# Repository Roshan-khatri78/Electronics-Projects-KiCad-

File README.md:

# ⚡ KiCad Projects Portfolio
 
A collection of electronics projects I designed in **KiCad**: schematics, PCB layouts, 3D models and, for many of them, Gerber files. I use it to learn by building, and every project here taught me something, including the mistakes. New projects get added as I go.

---
 
## 🌟 Featured: 4G GPS Tracker (4-layer)
 
[**Open the project folder →**](./4G-GPS-Tracker/)
 
My biggest and most complex design so far: a 4-layer 4G GPS tracker board with an ESP32-S3 and a 4G modem with built-in GNSS. I redrew the whole schematic by hand as hierarchical sheets, assigned every footprint and 3D model, then placed and routed the full board.
 
> **This is a design-only project.** It is based on the public Waveshare ESP32-S3-SIM7670X-4G schematic, which I redrew in KiCad. It is not an original circuit design, and I have not ordered, built or tested the board.
 
<!-- Add your images in 4G-GPS-Tracker/docs/ and keep these names, or change the paths -->

### What is on the board
 
- ESP32-S3 and a SIM7670X 4G modem with GNSS
- Battery charging and protection (ETA6098 charger, DW01 + 8205 protection), solar charge input (CN3791), MAX17048 fuel gauge
- USB-C, 18650 battery holder, SIM slot, microSD card, camera connector, MEMS microphone
- 3 u.FL antenna connectors (4G, GNSS, Wi-Fi/BT)
- W25Q128 flash, TXB0104 level shifter, CH343P USB-UART, push buttons, a DIP switch and pin headers
### Numbers
 
| | |
|---|---|
| Layers | 4 |
| Nets | 285 |
| Pads | 1000 |
| Vias | 564 |
| Capacitors / resistors | 90+ / 84+ |
| Footprint size for passives | 0805 (2012 metric) |
| KiCad version | 10.0.3 |
 
### Stackup and routing choices
 
| Layer | Use |
|---|---|
| F.Cu | Components, signals and the RF lines |
| In1.Cu | Solid GND plane |
| In2.Cu | Signal routing (no power pour, power is routed with traces) |
| B.Cu | Signals and the battery connections |
 
- The antenna lines are routed as **50 Ω microstrip** on F.Cu above the solid In1 GND plane. The width is about 0.35 mm for a 0.2 mm dielectric. This is a **calculated** value, not a measured one.
- Every GND pad gets a via straight down to the In1 plane, so the board has no long GND traces.
- Via sizes: 0.6 / 0.3 mm in general, and 0.5 / 0.25 mm in tight areas such as the camera fan-out.
- The crystal has no traces under it, and the SPI flash sits close to the ESP32.
### Status
 
- All nets are routed (0 unrouted).
- The KiCad DRC window crashed on this board, so I run DRC from the command line with `kicad-cli`, using a small script (in [`tools/`](./tools/)). It groups the violations by type, so I can see the real problems first.
- <!-- UPDATE this line after your final DRC run --> First DRC run: 0 unconnected items and 511 violations. Most of them were a via-size rule setting and cosmetic items (silkscreen, solder mask slivers). I am cleaning them up. A few minor violations may remain, so please **run DRC yourself before judging the layout**.
### Known limits
 
I want to be upfront about these:
 
- Power traces are 0.25 to 0.35 mm wide to fit the dense layout. A production board would use 1 mm or wider traces (or pours) for the modem supply, and several vias per layer change.
- A few vias are placed inside pads. A real factory would need filled and capped vias, or the vias would move beside the pads.
- The GNSS connector is far from the modem's GNSS pad, so that trace is longer than it should be. A final layout would move the connector closer.
- The camera part (U15) does not match yet. The schematic uses a 24-pin socket, and the footprint is the bare camera package.
- Nothing is simulated or measured: not the RF lines, not the power rails.
### What I learned
 
The first netlist update gave 47 errors from wrong footprints and missing library names. ERC complained about power outputs until I fixed the pin types on the GND pins. My first GNSS antenna trace was 68 mm long and ran on the back layer under the modem, so I deleted it and routed it again on the top layer. Along the way I learned about microstrip width, via sizes, fan-out under a camera footprint and why vias do not belong in small pads. Next I want to learn LTspice, to simulate the power blocks and filters.
 
**Credit:** schematic reference is the Waveshare ESP32-S3-SIM7670X-4G board design.
 
---
 
## 📖 About
 
The projects here go from simple beginner circuits to a 4-layer board with a 4G modem. Each one reflects real learning, including mistakes, revisions and improvements over time.
 
**Skills practiced**
 
- Schematic capture and symbol assignment, hierarchical multi-sheet schematics
- Footprint selection and custom footprint and symbol library creation
- PCB layout, trace routing, copper pours, 4-layer stackups
- RF trace width for 50 Ω microstrip (calculated)
- DRC, ERC and design rules, including command-line DRC
- Gerber export for fabrication
- 3D model linking and visualisation
---
 
## 🗂️ All projects
 
### ⚙️ Power conversion and batteries
 
| Project | What it is |
|---|---|
| [3V to 40V DC Booster](./3v%20to%2040v%20DC%20booster/) | Boost converter that steps 3 V up to as much as 40 V |
| [60W SMPS](./60W%20SMPS/) | 60 W switch-mode power supply |
| [DC-DC Buck Converter](./DC-DC%20Buck%20converter/) | XL4015 step-down converter with constant-current / constant-voltage output |
| [Battery Desulfator](./Battery%20Desulfator%20circuit/) | NE555 pulse generator driving an IRF244V MOSFET, for lead-acid batteries |
| [Battery Powered Bench Power Supply](./Battery%20powered%20bench%20power%20supply/) | Bench power supply that runs from batteries |
| [Li-ion 4S BMS](./Li-ion%204S%20BMS/) | Battery management board for a 4-cell Li-ion pack |
| [TP4056 Module](./tp4056%20module/) | TP4056 Li-ion battery charger module |
| [Multi-rail PDB](./multirail%20PDB/) | 24 V to 12 V, 5 V and 3.3 V buck cascade with a TI eFuse on each rail |
| [YX850 Power Failure Switching Module](./YX850%20Power%20Failure%20Automatic%20Switching%20Module/) | Automatic switch-over module for power failures |
| [Mini Inverter](./mini%20inverter/) | DC to AC inverter using IR2153 half-bridge gate drive |
| [Induction Heater](./inductionheater/) | High-frequency switching circuit that heats metal with a work coil |
 
### 🔧 Motor drivers and switching
 
| Project | What it is |
|---|---|
| [1-Channel Relay Driver](./1channelrelay/) | MMBT2222A switching a relay, with a flyback diode and a GND pour |
| [3-Phase BLDC Motor Controller](./3-Phase%20BLDC%20%28Brushless%20DC%29%20Motor%20Controller/) | Hierarchical design with IR2104 gate drivers and a 3-phase MOSFET bridge |
| [A4988 Stepper Motor Driver](./A4988%20Stepper%20Motor%20Driver/) | Stepper motor driver board based on the A4988 |
| [L298 Motor Driver](./L298%20motor%20driver/) | Dual H-bridge driver for two DC motors or one stepper motor |
| [Dual VNH2SP30 Motor Driver](./Dual%20VNH2SP30%20Motor%20Driver%20Carrier%20MD03A/) | Carrier board for the dual VNH2SP30 high-current motor driver |
| [Solid-state Relay](./Solid-state%20relay/) | Solid-state relay circuit |
 
### 📡 Wireless, GNSS and radio
 
| Project | What it is |
|---|---|
| [4G GPS Tracker](./4G-GPS-Tracker/) | **Featured.** 4-layer board with ESP32-S3 and a 4G modem with GNSS |
| [Embedded GSM_GPS IoT Controller](./Embedded%20GSM_GPS%20IoT%20Controller/) | IoT controller board with GSM and GPS |
| [GSM_GPS Embedded Development Board](./GSM_GPS%20Embedded%20Development%20Board/) | Development board with GSM and GPS |
| [HC-06 Bluetooth Module](./HC-06%20BLUETOOTH%C2%AE%20Module/) | Breakout board for the HC-06 Bluetooth serial module |
| [Digital Radio Receiver](./microcontroller-controlled%20digital%20radio%20receiver/) | Microcontroller-tuned FM/AM radio receiver |
| [Portable FM Radio Receiver](./portable%20FM%20radio%20receiver/) | Battery-powered FM radio with an M6955 receiver IC and an Arduino Pro Mini |
| [FMCW Radar](./FMCW%20Radar/) | FMCW radar board |
| [Wake on LAN](./Wake%20on%20LAN/) | Wake-on-LAN board |
 
### 🧠 Microcontroller and computer boards
 
| Project | What it is |
|---|---|
| [Arduino Uno R3 Clone](./Arduino%20R3/) | Clone of the Arduino Uno R3 with the ATmega328P |
| [STM32 Dev Board](./STM32%20DEV%20board/) | STM32 board with reset, boot selection, crystal and programming header |
| [ESP32 Demo Project](./esp32%20demo%20project/) | ESP32 module board exploring power, GPIO and boot strapping pins |
| [ESP32-S3](./ESP32-S3/) | ESP32-S3 based board |
| [ESP32 Drone](./esp32Drone/) | ESP32 flight controller with IMU, ESC outputs and USB-C, 4 layers |
| [Mini Drone](./minidrone/) | Small drone board |
| [Raspberry Pi Pico](./rasberry%20pi%20pico/) | Raspberry Pi Pico board design |
| [Raspberry Pi CM4 Carrier Board](./Raspberry%20Pi%20Compute%20Module%204%20Carrier%20Board/) | Carrier board for the Raspberry Pi Compute Module 4 |
| [Milk-V Duo Module](./Milk-V%20Duo%20Module/) | Board design for the Milk-V Duo |
| [LoFive](./LoFive/) | RISC-V board based on the open-source LoFive design |
| [USB to UART Converter](./USB2UART/) | USB-serial bridge board for programming and debugging microcontrollers |
 
### 🔬 Sensors, analog, instruments and basics
 
| Project | What it is |
|---|---|
| [ESP32 Oscilloscope and Function Generator](./esp32%20oscilloscope%20adn%20fucntion%20generator/) 🎓 | **Final year project.** Signal acquisition and signal generation on one ESP32 board |
| [Air Quality Sensor Board](./Air%20Quality%20Sensor%20Board/) | Air quality sensor with an MCU and a Tag-Connect SWD footprint |
| [DS3231 RTC Module](./DS3231%20RTC%20Module/) | Real-time clock breakout with battery backup |
| [SPO2 Pulse Oximeter](./SPO2/) | Red and IR LEDs with a photodetector for SpO2 and heart rate |
| [VL53L0X ToF Distance Sensor](./VL53L0X%20Time-of-Flight%20Distance%20Sensor/) | Breakout for the VL53L0X time-of-flight sensor |
| [LM386 Audio Amplifier](./LM386%20Based%20Audio%20Amplifier/) | Small audio amplifier built around the LM386 |
| [Hearing Aid](./hearingaid/) | Hearing-aid amplifier with an electret mic, BC547 transistor stages and a 16 Ω earpiece on 3 V |
| [LED Flasher](./LED%20flasher/) | Astable multivibrator LED flasher |
| [One Digit Up/Down Counter](./one%20digit%20updown%20counter/) | Up/down counter with a 7-segment display |
| [Traffic Light Controller](./Traffic%20light%20controller/) | Traffic light controller circuit |
 
---
 
## 📁 Repository structure
 
Each project has its own folder. Most contain:
 
```
<project-name>/
├── *.kicad_sch      # Schematic files
├── *.kicad_pcb      # PCB layout files
└── Gerber/          # Fabrication files, where exported
```
 
The featured project also has a `docs/` folder with the 3D images and a `tools/` folder at the repository root with the command-line DRC script.
 
---
 
## 🛠️ Tools
 
- **KiCad EDA** v10.0
- `kicad-cli` for command-line DRC
- Manufacturer data sheets for part selection
- KiCad 3D viewer for visual inspection
- Custom symbol and footprint libraries
---
 
## 📝 Note on quality
 
These projects document my learning openly. Some designs have flaws or open points, and I list them where I know them. I come back and improve designs as my knowledge grows, instead of hiding earlier work.
 
---
 
## 📄 License
 
Unless stated otherwise, the projects here are shared for education and as a portfolio. Designs that are based on other people's work (for example the Waveshare reference design) belong to their original authors, and I credit them in each project.
 
Feel free to open an issue or a discussion if you have suggestions or feedback.

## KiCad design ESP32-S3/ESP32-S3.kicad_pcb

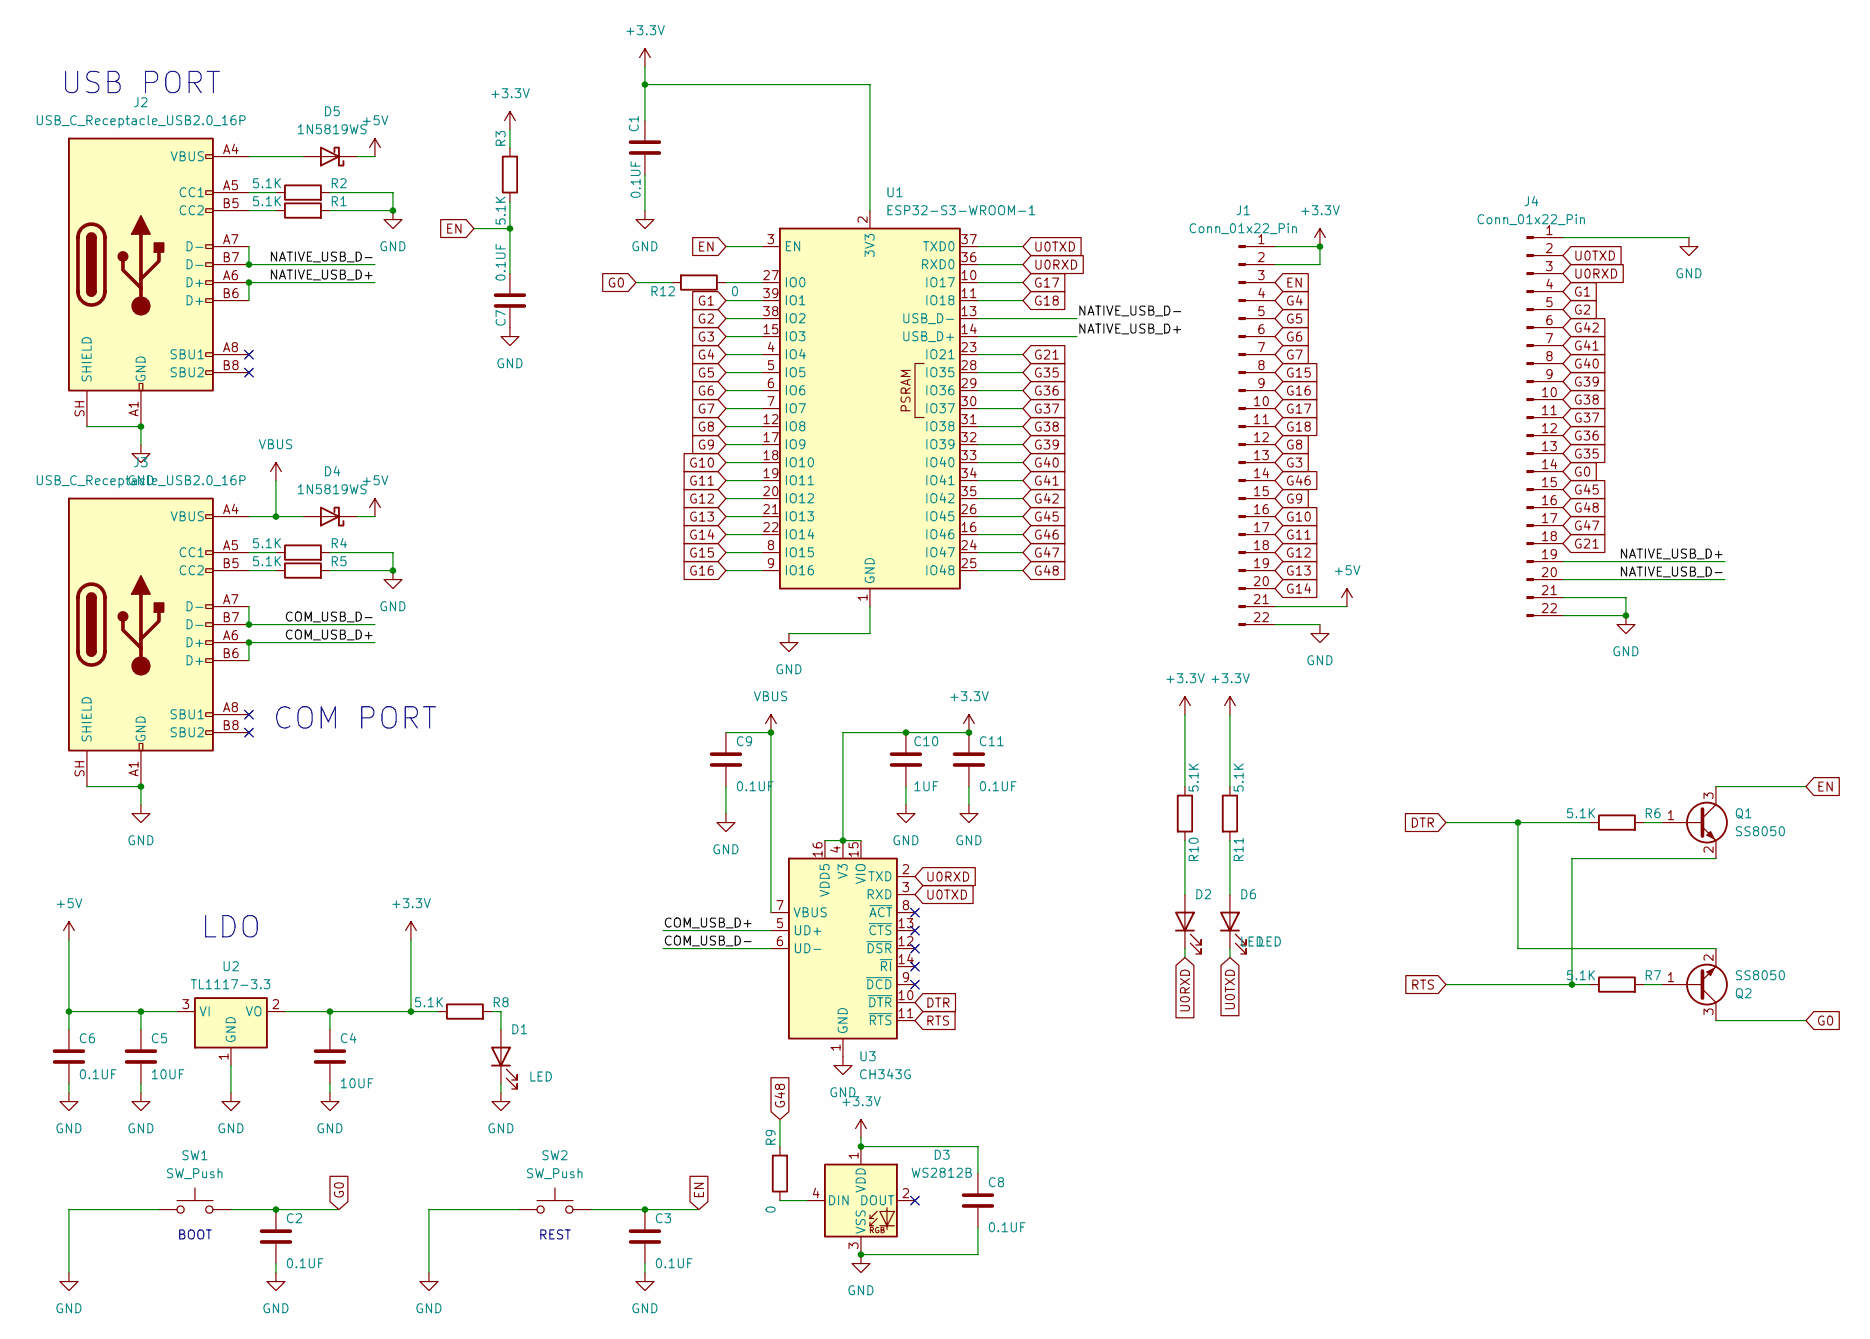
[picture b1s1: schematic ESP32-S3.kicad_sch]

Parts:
C1, C2, C3, C6, C7, C8, C9, C11: 0.1UF; C_0603_1608Metric
C4, C5: 10UF; C_0805_2012Metric
C10: 1UF; C_0603_1608Metric
D1, D2, D6: LED; LED_0603_1608Metric_Pad1.05x0.95mm_HandSolder
D3: WS2812B; LED_WS2812B_PLCC4_5.0x5.0mm_P3.2mm
D4, D5: 1N5819WS; D_SOD-323
J1, J4: Conn_01x22_Pin; PinHeader_1x22_P2.54mm_Vertical
J2, J3: USB_C_Receptacle_USB2.0_16P; USB_C_Receptacle_GCT_USB4105-xx-A_16P_TopMnt_Horizontal
Q1, Q2: SS8050; SOT-23
R1, R2, R3, R4, R5, R6, R7, R8, R10, R11: 5.1K; R_0603_1608Metric
R9, R12: 0; R_0603_1608Metric
SW1, SW2: SW_Push; SW_SPST_PTS810
U1: ESP32-S3-WROOM-1
U2: TL1117-3.3; SOT-223-3_TabPin2
U3: CH343G; SOIC-16_3.9x9.9mm_P1.27mm

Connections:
+3.3V: C1.1, C4.1, C8.1, C10.2, C11.2, D3.1 (VDD), J1.1, J1.2, R3.2, R8.1, R10.1, R11.1, U1.2 (3V3), U2.2 (VO), U3.4 (V3), U3.15 (VIO), U3.16 (VDD5)
+5V: C5.1, C6.1, D4.1 (K), D5.1 (K), J1.21, U2.3 (VI)
/COM_USB_D+: J3.A6 (D+), J3.B6 (D+), U3.5 (UD+)
/COM_USB_D-: J3.A7 (D-), J3.B7 (D-), U3.6 (UD-)
/NATIVE_USB_D+: J2.A6 (D+), J2.B6 (D+), J4.19, U1.14 (USB_D+)
/NATIVE_USB_D-: J2.A7 (D-), J2.B7 (D-), J4.20, U1.13 (USB_D-)
DTR: Q2.2 (E), R6.1, U3.10 (~DTR)
EN: C3.1, C7.1, J1.3, Q1.3 (C), R3.1, SW2.2, U1.3 (EN); also elsewhere on the board
G0: C2.1, J4.14, Q2.3 (C), R12.2, SW1.2; also elsewhere on the board
G1: J4.4, U1.39 (IO1)
G2: J4.5, U1.38 (IO2)
G3: J1.13, U1.15 (IO3)
G4: J1.4, U1.4 (IO4)
G5: J1.5, U1.5 (IO5)
G6: J1.6, U1.6 (IO6)
G7: J1.7, U1.7 (IO7)
G8: J1.12, U1.12 (IO8)
G9: J1.15, U1.17 (IO9)
G10: J1.16, U1.18 (IO10)
G11: J1.17, U1.19 (IO11)
G12: J1.18, U1.20 (IO12)
G13: J1.19, U1.21 (IO13)
G14: J1.20, U1.22 (IO14)
G15: J1.8, U1.8 (IO15)
G16: J1.9, U1.9 (IO16)
G17: J1.10, U1.10 (IO17)
G18: J1.11, U1.11 (IO18)
G21: J4.18, U1.23 (IO21)
G35: J4.13, U1.28 (IO35)
G36: J4.12, U1.29 (IO36)
G37: J4.11, U1.30 (IO37)
G38: J4.10, U1.31 (IO38)
G39: J4.9, U1.32 (IO39)
G40: J4.8, U1.33 (IO40)
G41: J4.7, U1.34 (IO41)
G42: J4.6, U1.35 (IO42)
G45: J4.15, U1.26 (IO45)
G46: J1.14, U1.16 (IO46)
G47: J4.17, U1.24 (IO47)
G48: J4.16, R9.2, U1.25 (IO48)
GND: C1.2, C2.2, C3.2, C4.2, C5.2, C6.2, C7.2, C8.2, C9.1, C10.1, C11.1, D1.1 (K), D3.3 (VSS), J1.22, J2.A1 (GND), J2.A12 (GND), J2.B1 (GND), J2.B12 (GND), J2.SH (SHIELD), J3.A1 (GND), J3.A12 (GND), J3.B1 (GND), J3.B12 (GND), J3.SH (SHIELD), J4.1, J4.21, J4.22, R1.2, R2.2, R4.2, R5.2, SW1.1, SW2.1, U1.1 (GND), U1.40 (GND), U1.41 (GND), U2.1 (GND), U3.1 (GND); also elsewhere on the board
unnamed: D1.2 (A), R8.2
unnamed: D2.2 (A), R10.2
unnamed: D3.4 (DIN), R9.1
unnamed: D5.2 (A), J2.A4 (VBUS), J2.A9 (VBUS), J2.B4 (VBUS), J2.B9 (VBUS)
unnamed: D6.2 (A), R11.2
unnamed: J2.A5 (CC1), R2.1
unnamed: J2.B5 (CC2), R1.1
unnamed: J3.A5 (CC1), R4.1
unnamed: J3.B5 (CC2), R5.1
unnamed: Q1.1 (B), R6.2
unnamed: Q2.1 (B), R7.2
unnamed: R12.1, U1.27 (IO0)
RTS: Q1.2 (E), R7.1, U3.11 (~RTS)
U0RXD: D2.1 (K), J4.3, U1.36 (RXD0), U3.2 (TXD)
U0TXD: D6.1 (K), J4.2, U1.37 (TXD0), U3.3 (RXD)
VBUS: C9.2, D4.2 (A), J3.A4 (VBUS), J3.A9 (VBUS), J3.B4 (VBUS), J3.B9 (VBUS), U3.7 (VBUS)

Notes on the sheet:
COM PORT
REST
LDO
USB PORT
BOOT

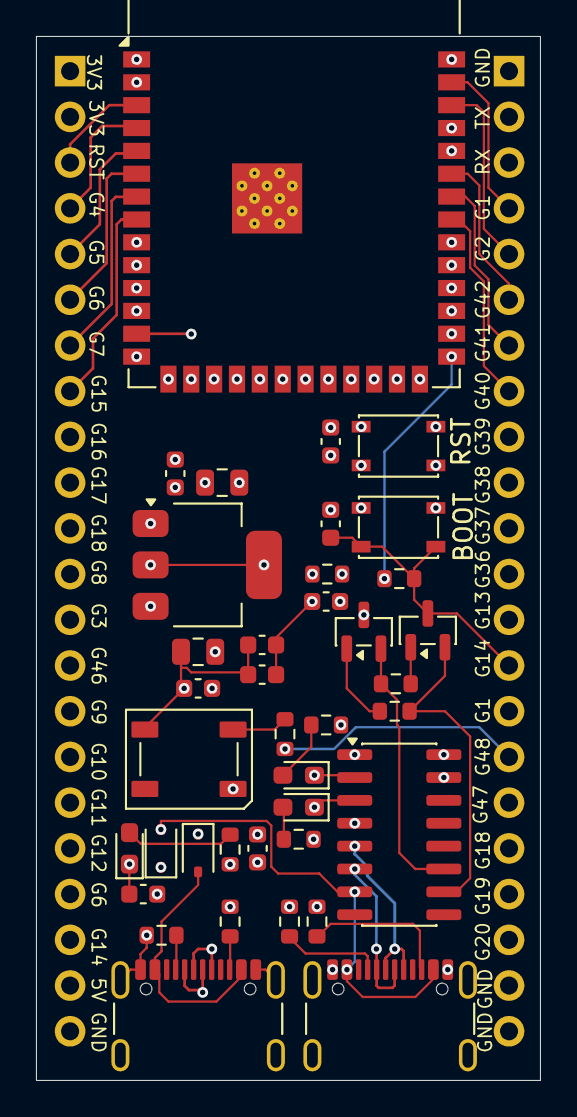
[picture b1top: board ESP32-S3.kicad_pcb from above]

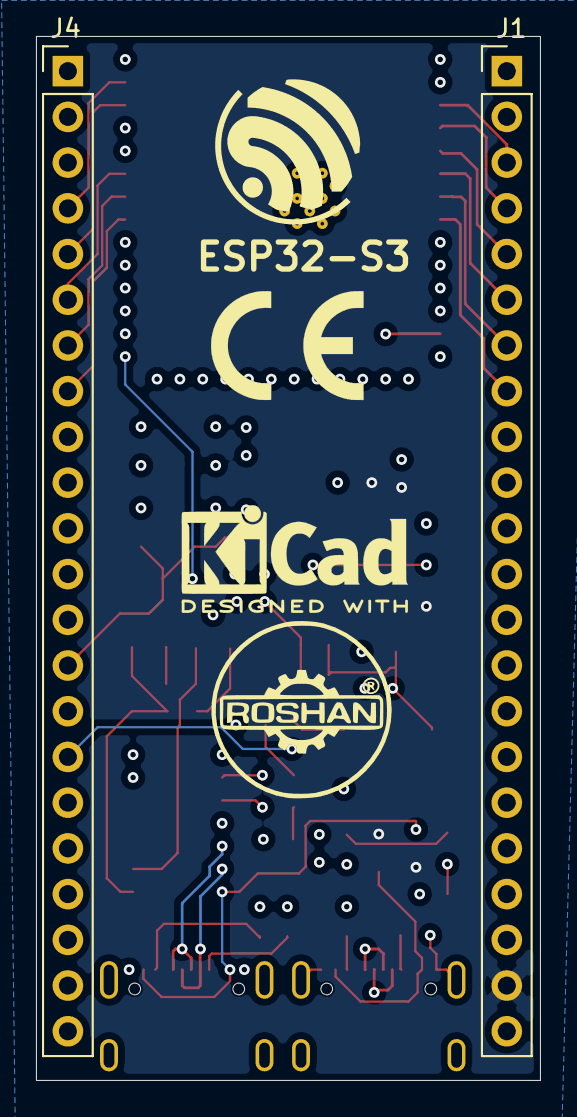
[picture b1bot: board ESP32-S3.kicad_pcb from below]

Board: 4 copper layers, 28.0 x 58.0 mm, 40 parts (2 on the bottom side), 57 nets.

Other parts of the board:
BOOT: SW_Push; SW_SPST_PTS810
RST: SW_Push; SW_SPST_PTS810

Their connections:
EN: RST.2; also elsewhere on the board
G0: BOOT.2; also elsewhere on the board
GND: BOOT.1, RST.1; also elsewhere on the board
